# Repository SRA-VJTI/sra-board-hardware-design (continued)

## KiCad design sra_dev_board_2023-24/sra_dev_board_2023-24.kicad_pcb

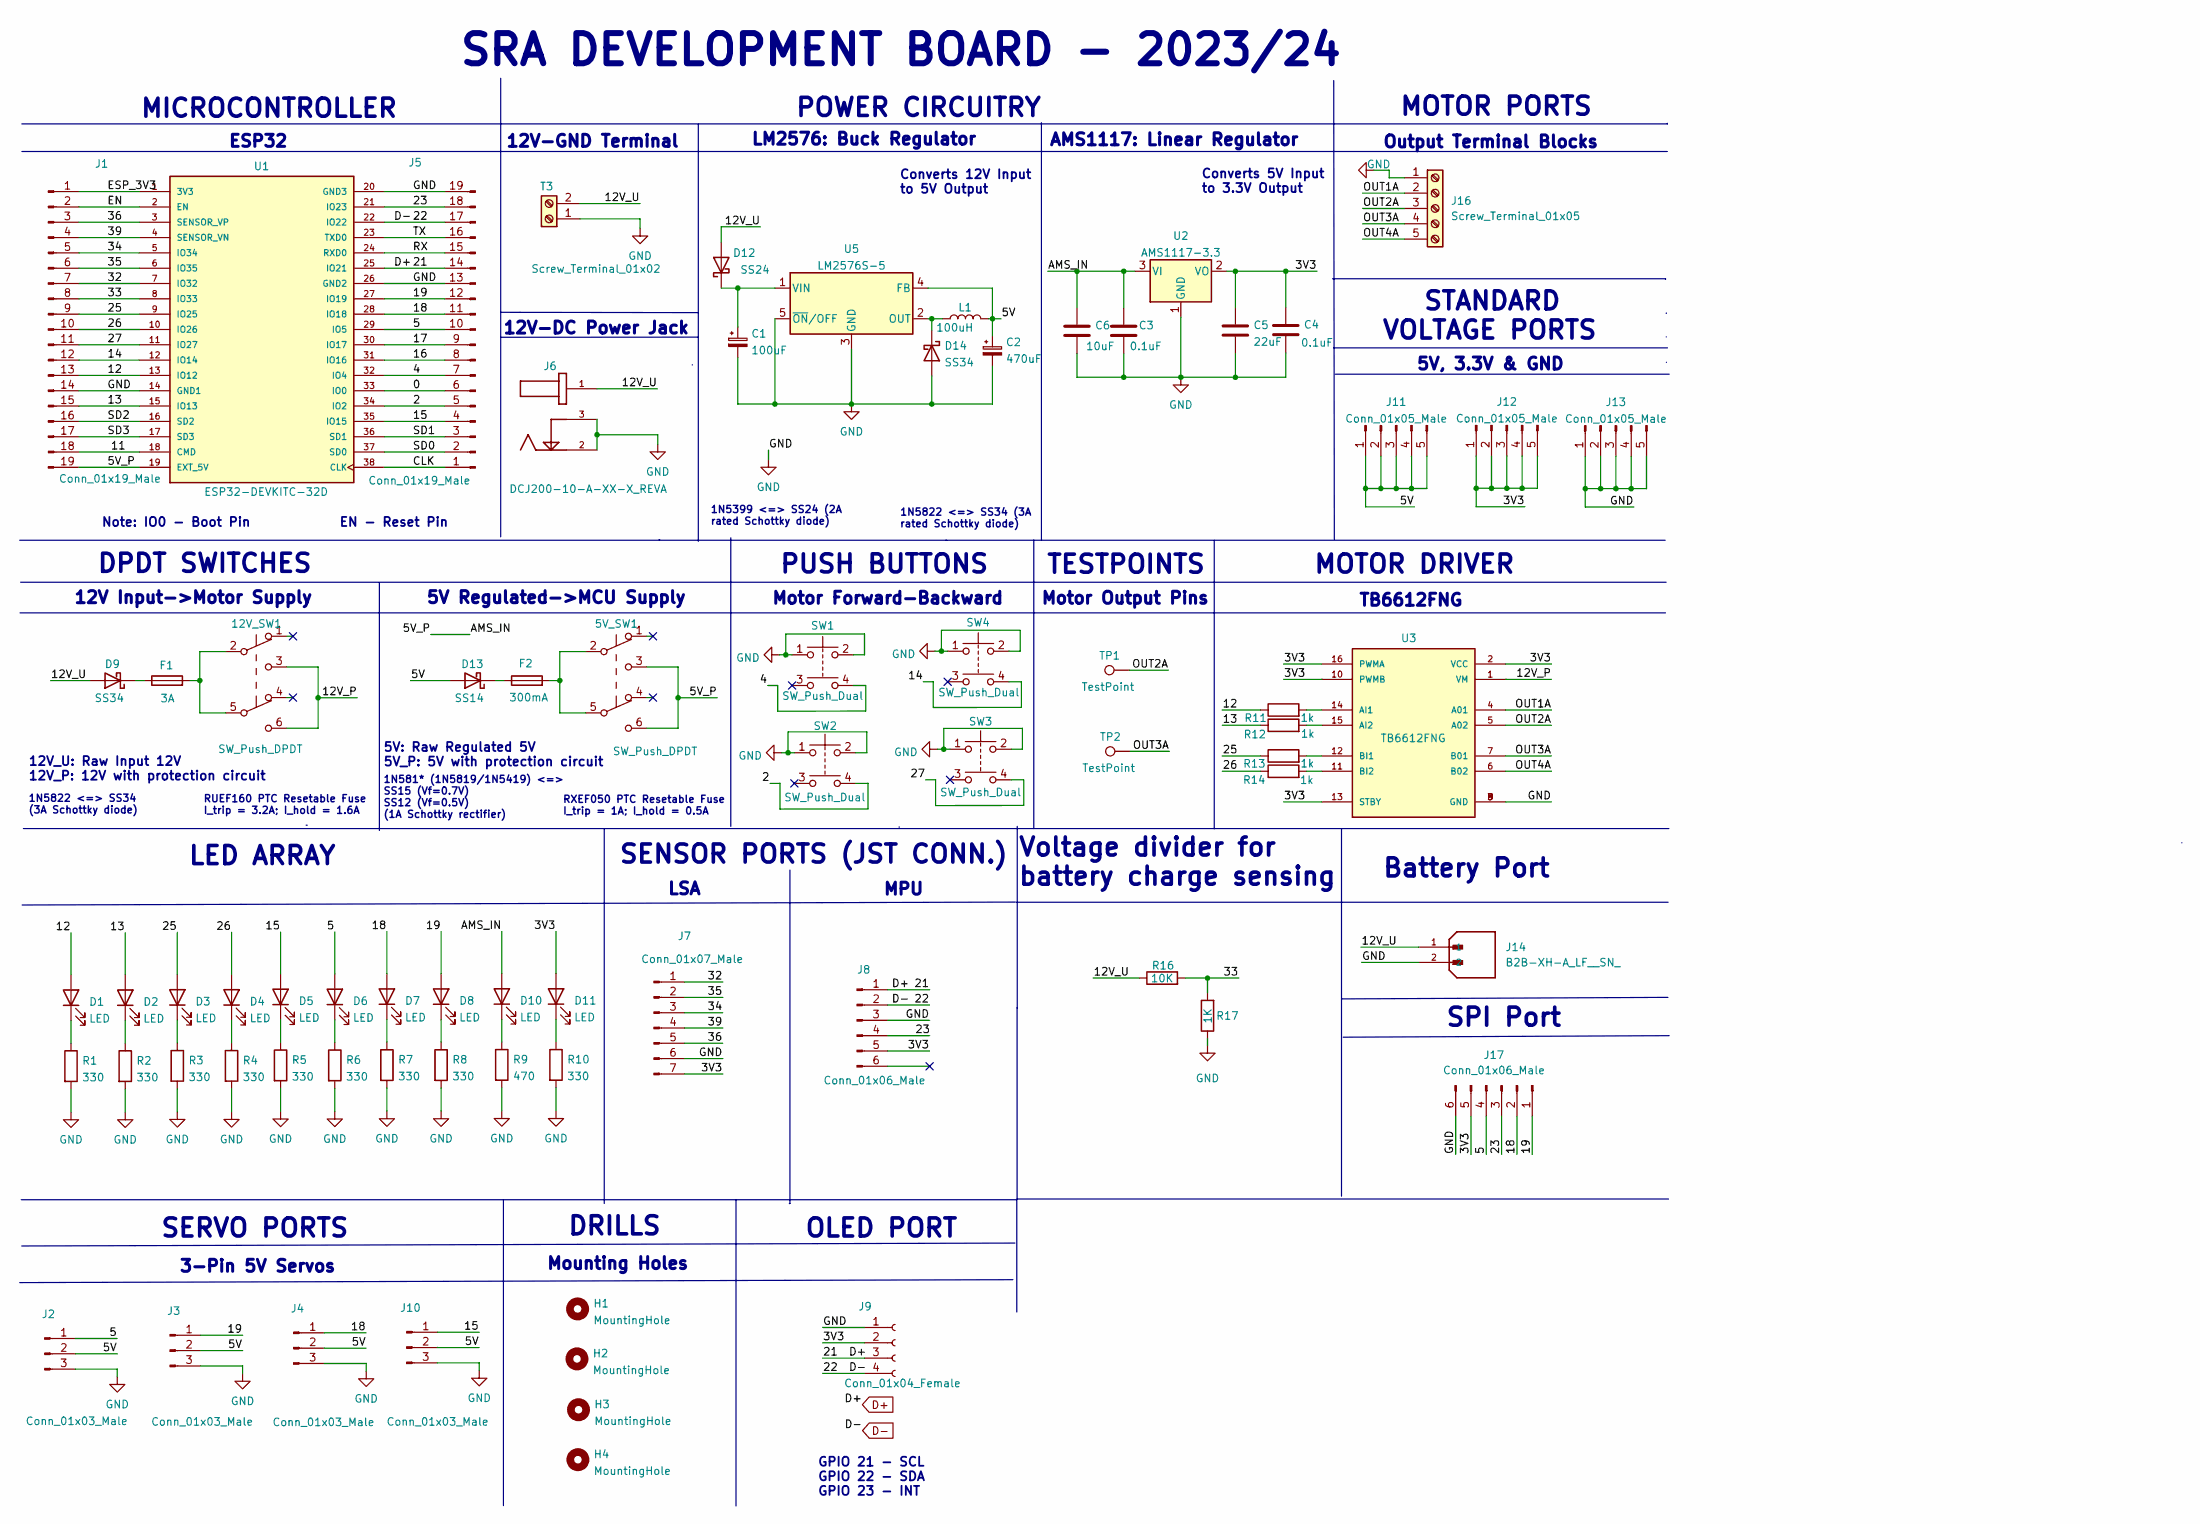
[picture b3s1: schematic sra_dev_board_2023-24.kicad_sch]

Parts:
5V_SW1, 12V_SW1: SW_Push_DPDT; dpdt_sw_2x03_tht
C1: 100uF; CP_Elec_6.3x7.7
C2: 470uF; CP_Elec_8x10
C3, C4: 0.1uF; C_0603_1608Metric
C5: 22uF; C_0603_1608Metric
C6: 10uF; C_0603_1608Metric
D1, D2, D3, D4, D5, D6, D7, D8, D10, D11: LED; LED_0603_1608Metric
D9, D14: SS34; D_SMB
D12: SS24; D_SMA
D13: SS14; D_SMA
F1: 3A; RUEF160
F2: 300mA; RXEF050
H1, H2, H3, H4: MountingHole; MountingHole_3.2mm_M3
J1, J5: Conn_01x19_Male; 1X19
J2, J3, J4, J10: Conn_01x03_Male; 1X03
J6: DCJ200-10-A-XX-X_REVA; BarrelJack_Wuerth_6941xx301002
J7: Conn_01x07_Male; PinHeader_1x07_P2.54mm_Vertical
J8, J17: Conn_01x06_Male; PinHeader_1x06_P2.54mm_Vertical
J9: Conn_01x04_Female; 1X04
J11, J12, J13: Conn_01x05_Male; 1X05
J14: B2B-XH-A_LF__SN_; JST_B2B-XH-A_LF__SN_; PARTREV N/A
J16: Screw_Terminal_01x05; TerminalBlock_bornier-5_P5.08mm
L1: 100uH; CDRH127_inductor_smd
R1, R2, R3, R4, R5, R6, R7, R8, R10: 330; R_0603_1608Metric
R9: 470; R_0603_1608Metric
R11, R12, R13, R14: 1k; R_1206_3216Metric
R16: 10K; R_1206_3216Metric
R17: 1K; R_1206_3216Metric
SW1, SW2, SW3, SW4: SW_Push_Dual; spst_tactile_sw_2x02_smd
T3: Screw_Terminal_01x02; 12V_1x02_tht
TP1, TP2: TestPoint; pad_1,27-2,54_smd
U1: ESP32-DEVKITC-32D; ESP32-DEVKITCv4-32D; PARTREV 4
U2: AMS1117-3.3; SOT-223-3_TabPin2
U3: TB6612FNG; TB6612FNG_2; PARTREV 11-13-17
U5: LM2576S-5; TO-263-5_TabPin3

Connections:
/0: J5.6, U1.33 (IO0)
/2: J5.5, SW2.4, U1.34 (IO2)
/3V3: C4.1, C5.1, D11.2 (A), J7.7, J8.5, J9.2, J12.1, J12.2, J12.3, J12.4, J12.5, J17.5, U2.2 (VO), U3.2 (VCC), U3.10 (PWMB), U3.13 (STBY), U3.16 (PWMA)
/4: J5.7, SW1.4, U1.32 (IO4)
/5: D6.2 (A), J2.1, J5.10, J17.4, U1.29 (IO5)
/5V: C2.1, D13.2 (A), J2.2, J3.2, J4.2, J10.2, J11.1, J11.2, J11.3, J11.4, J11.5, L1.2, U5.4 (FB)
/5V_P: 5V_SW1.3 (C), 5V_SW1.6 (C), C3.1, C6.1, D10.2 (A), J1.19, U1.19 (EXT_5V), U2.3 (VI)
/11: J1.18, U1.18 (CMD)
/12: D1.2 (A), J1.13, R11.1, U1.13 (IO12)
/12V_P: 12V_SW1.3 (C), 12V_SW1.6 (C), U3.1 (VM)
/12V_U: D9.2 (A), D12.2 (A), J6.1, J14.1, R16.1, T3.2
/13: D2.2 (A), J1.15, R12.1, U1.15 (IO13)
/14: J1.12, SW4.4, U1.12 (IO14)
/15: D5.2 (A), J5.4, J10.1, U1.35 (IO15)
/16: J5.8, U1.31 (IO16)
/17: J5.9, U1.30 (IO17)
/18: D7.2 (A), J4.1, J5.11, J17.2, U1.28 (IO18)
/19: D8.2 (A), J3.1, J5.12, J17.1, U1.27 (IO19)
/23: J5.18, J8.4, J17.3, U1.21 (IO23)
/25: D3.2 (A), J1.9, R13.1, U1.9 (IO25)
/26: D4.2 (A), J1.10, R14.1, U1.10 (IO26)
/27: J1.11, SW3.4, U1.11 (IO27)
/32: J1.7, J7.1, U1.7 (IO32)
/33: J1.8, R16.2, R17.2, U1.8 (IO33)
/34: J1.5, J7.3, U1.5 (IO34)
/35: J1.6, J7.2, U1.6 (IO35)
/36: J1.3, J7.5, U1.3 (SENSOR_VP)
/39: J1.4, J7.4, U1.4 (SENSOR_VN)
/CLK: J5.1, U1.38 (CLK)
/EN: J1.2, U1.2 (EN)
/ESP_3V3: J1.1, U1.1 (3V3)
/OUT1A: J16.2, U3.4 (A01)
/OUT2A: J16.3, TP1.1, U3.5 (A02)
/OUT3A: J16.4, TP2.1, U3.7 (B01)
/OUT4A: J16.5, U3.6 (B02)
/RX: J5.15, U1.24 (RXD0)
/SD0: J5.2, U1.37 (SD0)
/SD1: J5.3, U1.36 (SD1)
/SD2: J1.16, U1.16 (SD2)
/SD3: J1.17, U1.17 (SD3)
/TX: J5.16, U1.23 (TXD0)
D+: J5.14, J8.1, J9.3, U1.25 (IO21)
D-: J5.17, J8.2, J9.4, U1.22 (IO22)
GND: C1.2, C2.2, C3.2, C4.2, C5.2, C6.2, D14.2 (A), J1.14, J2.3, J3.3, J4.3, J5.13, J5.19, J6.2, J6.3, J7.6, J8.3, J9.1, J10.3, J13.1, J13.2, J13.3, J13.4, J13.5, J14.2, J16.1, J17.6, R1.2, R2.2, R3.2, R4.2, R5.2, R6.2, R7.2, R8.2, R9.2, R10.2, R17.1, SW1.1, SW1.2, SW2.1, SW2.2, SW3.1, SW3.2, SW4.1, SW4.2, T3.1, U1.14 (GND1), U1.20 (GND3), U1.26 (GND2), U2.1 (GND), U3.3 (GND), U3.8 (GND), U3.9 (GND), U5.3 (GND), U5.5 (~ON/OFF)
unnamed: 5V_SW1.2 (B), 5V_SW1.5 (B), F2.2
unnamed: 12V_SW1.2 (B), 12V_SW1.5 (B), F1.2
unnamed: D1.1 (K), R1.1
unnamed: D2.1 (K), R2.1
unnamed: D3.1 (K), R3.1
unnamed: D4.1 (K), R4.1
unnamed: D5.1 (K), R5.1
unnamed: D6.1 (K), R6.1
unnamed: D7.1 (K), R7.1
unnamed: D8.1 (K), R8.1
unnamed: D9.1 (K), F1.1
unnamed: D10.1 (K), R9.1
unnamed: D11.1 (K), R10.1
unnamed: C1.1, D12.1 (K), U5.1 (VIN)
unnamed: D13.1 (K), F2.1
unnamed: D14.1 (K), L1.1, U5.2 (OUT)
unnamed: R11.2, U3.14 (AI1)
unnamed: R12.2, U3.15 (AI2)
unnamed: R13.2, U3.12 (BI1)
unnamed: R14.2, U3.11 (BI2)

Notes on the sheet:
5V, 3.3V & GND
RXEF050 PTC Resetable Fuse I_trip = 1A; I_hold = 0.5A
Mounting Holes
SRA DEVELOPMENT BOARD - 2023/24
LED ARRAY
12V_U: Raw Input 12V 12V_P: 12V with protection circuit
12V-GND Terminal
1N5822 <=> SS34 (3A rated Schottky diode)
Output Terminal Blocks
LSA
MPU
Converts 5V Input to 3.3V Output
DRILLS
SENSOR PORTS (JST CONN.)
1N5399 <=> SS24 (2A rated Schottky diode)
DPDT SWITCHES
5V: Raw Regulated 5V 5V_P: 5V with protection circuit
Note: IO0 - Boot Pin EN - Reset Pin
POWER CIRCUITRY
ESP32
RUEF160 PTC Resetable Fuse I_trip = 3.2A; I_hold = 1.6A
LM2576: Buck Regulator
MICROCONTROLLER
Battery Port
GPIO 21 - SCL GPIO 22 - SDA GPIO 23 - INT
TB6612FNG
1N5822 <=> SS34 (3A Schottky diode)
3-Pin 5V Servos
SERVO PORTS
Voltage divider for battery charge sensing
1N581* (1N5819/1N5419) <=> SS15 (Vf=0.7V) SS12 (Vf=0.5V) (1A Schottky rectifier)
12V Input->Motor Supply
SPI Port
5V Regulated->MCU Supply
OLED PORT
MOTOR PORTS
Motor Output Pins
MOTOR DRIVER
12V-DC Power Jack
Converts 12V Input to 5V Output

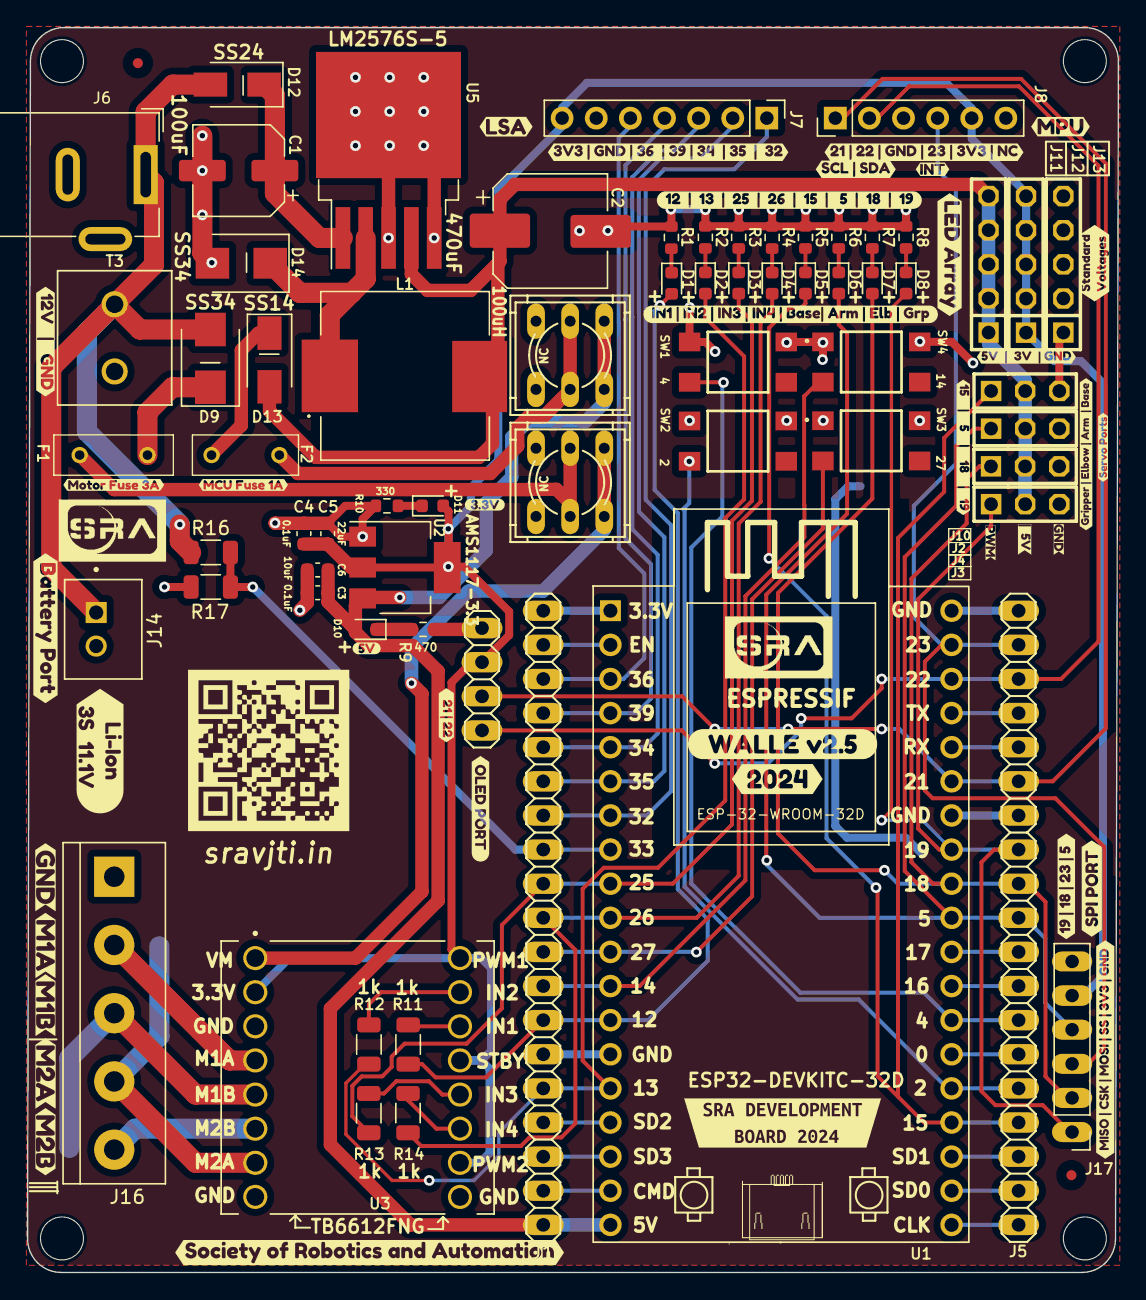
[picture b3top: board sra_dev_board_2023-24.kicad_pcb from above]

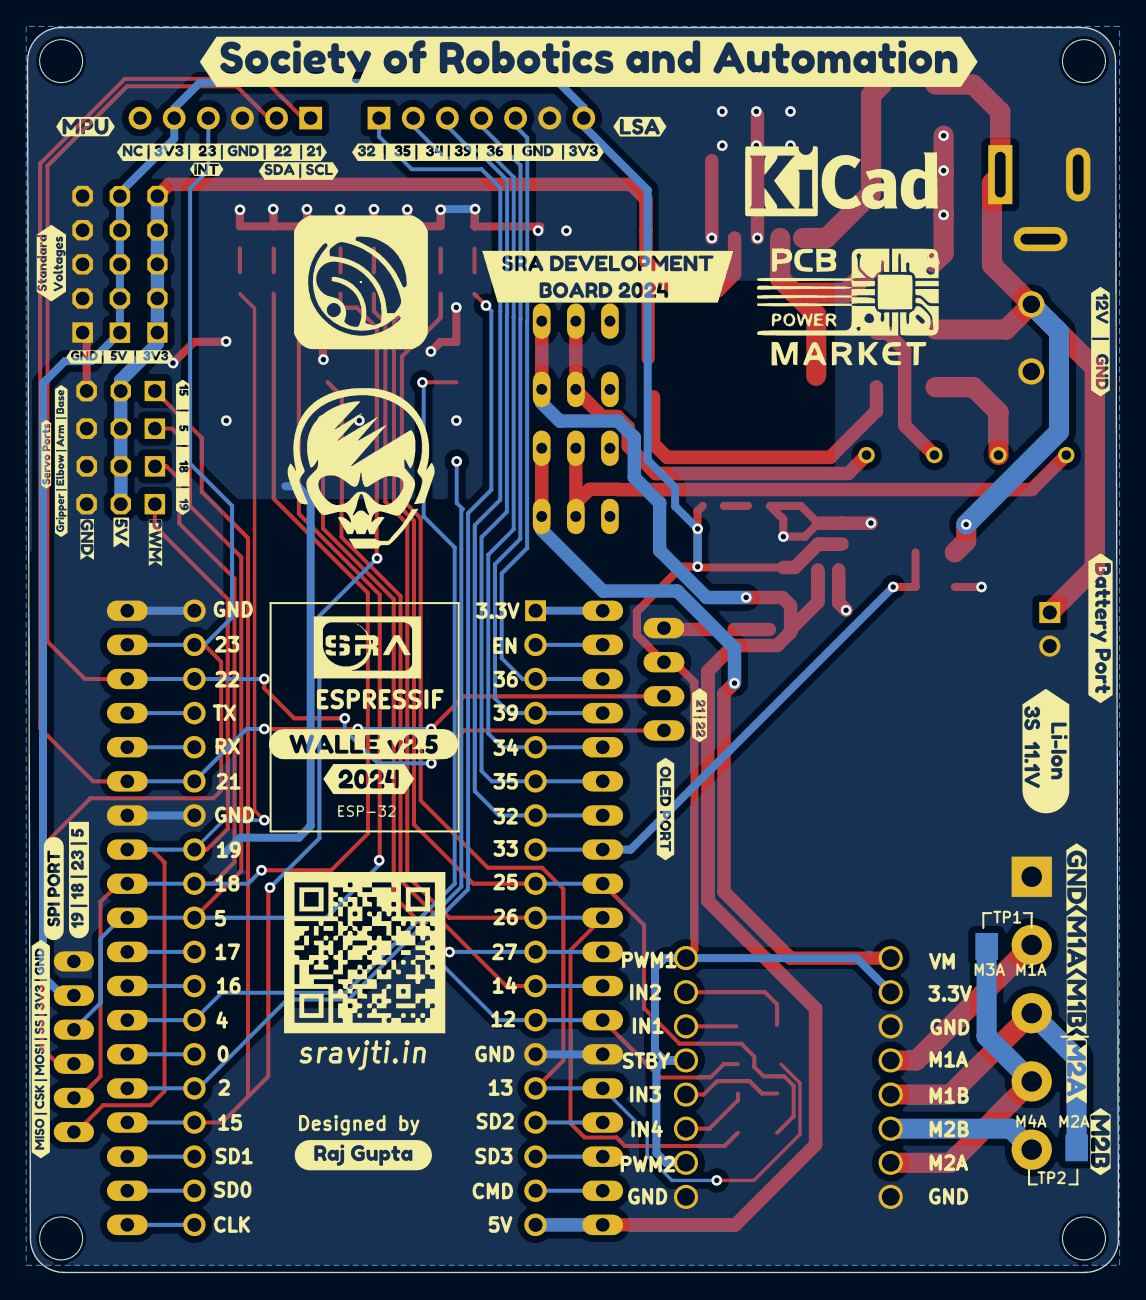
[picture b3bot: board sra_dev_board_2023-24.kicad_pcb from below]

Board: 2 copper layers, 81.2 x 92.7 mm, 142 parts (32 on the bottom side), 64 nets.

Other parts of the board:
kibuzzard-637A08DA, kibuzzard-637A08DA#2: G***; kibuzzard-637A08DA
kibuzzard-637B5F12: G***; kibuzzard-637B5F12
kibuzzard-637B5F60: G***; kibuzzard-637B5F60
kibuzzard-637B65B8: G***; kibuzzard-637B65B8
kibuzzard-658F2ACB: G***; kibuzzard-658F2ACB
kibuzzard-658F2B02: G***; kibuzzard-658F2B02
kibuzzard-658F2B2A: G***; kibuzzard-658F2B2A
kibuzzard-658F2C3C, kibuzzard-658F2C3C#2: G***; kibuzzard-658F2C3C
kibuzzard-658F2C13, kibuzzard-658F2C13#2: G***; kibuzzard-658F2C13
kibuzzard-658F2C67, kibuzzard-658F2C67#2: G***; kibuzzard-658F2C67
kibuzzard-658F2DCD: G***; kibuzzard-658F2DCD
kibuzzard-658F2DEA: G***; kibuzzard-658F2DEA
kibuzzard-658F2DF6: G***; kibuzzard-658F2DF6
kibuzzard-658F2E2C, kibuzzard-658F2E2C#2: G***; kibuzzard-658F2E2C
kibuzzard-658F2E4A, kibuzzard-658F2E4A#2: G***; kibuzzard-658F2E4A
kibuzzard-658F2E5A, kibuzzard-658F2E5A#2: G***; kibuzzard-658F2E5A
kibuzzard-658F2E6C, kibuzzard-658F2E6C#2: G***; kibuzzard-658F2E6C
kibuzzard-658F9F93, kibuzzard-658F9F93#2: G***; kibuzzard-658F9F93
kibuzzard-658F9FD8: G***; kibuzzard-658F9FD8
kibuzzard-658F289E: G***; kibuzzard-658F289E
kibuzzard-658F2903: G***; kibuzzard-658F2903
kibuzzard-658FA1D8: G***; kibuzzard-658FA1D8
kibuzzard-658FA19E: G***; kibuzzard-658FA19E
kibuzzard-658FA187, kibuzzard-658FA187#2: G***; kibuzzard-658FA187
kibuzzard-658FA201: G***; kibuzzard-658FA201
kibuzzard-6587FF3E: G***; kibuzzard-6587FF3E
kibuzzard-6587FF20: G***; kibuzzard-6587FF20
kibuzzard-6587FF29: G***; kibuzzard-6587FF29
kibuzzard-63775DBB, kibuzzard-63775DBB#2: G***; kibuzzard-63775DBB
kibuzzard-63777F1B: G***; kibuzzard-63777F1B
kibuzzard-65916C1A: G***; kibuzzard-65916C1A
kibuzzard-65916C11: G***; kibuzzard-65916C11
kibuzzard-65916C31: G***; kibuzzard-65916C31
kibuzzard-65916C76, kibuzzard-65916C76#2: G***; kibuzzard-65916C76
kibuzzard-65916D2D, kibuzzard-65916D2D#2: G***; kibuzzard-65916D2D
kibuzzard-653918A0: G***; kibuzzard-653918A0
kibuzzard-653918AE: G***; kibuzzard-653918AE
kibuzzard-653918C1: G***; kibuzzard-653918C1
kibuzzard-659161DE: G***; kibuzzard-659161DE
kibuzzard-659162C0: G***; kibuzzard-659162C0
kibuzzard-659163CD: G***; kibuzzard-659163CD
kibuzzard-659163E0: G***; kibuzzard-659163E0
kibuzzard-659164BA: G***; kibuzzard-659164BA
kibuzzard-659189BF, kibuzzard-659189BF#2: G***; kibuzzard-659189BF
kibuzzard-659189DA, kibuzzard-659189DA#2: G***; kibuzzard-659189DA
kibuzzard-6539189A: G***; kibuzzard-6539189A
kibuzzard-6591639C: G***; kibuzzard-6591639C
kibuzzard-6591649B: G***; kibuzzard-6591649B
kibuzzard-6591664B: G***; kibuzzard-6591664B
kibuzzard-6591665D: G***; kibuzzard-6591665D
kibuzzard-65916111: G***; kibuzzard-65916111
kibuzzard-65916213: G***; kibuzzard-65916213
kibuzzard-65918321: G***; kibuzzard-65918321
kibuzzard-65919040, kibuzzard-65919040#2: G***; kibuzzard-65919040

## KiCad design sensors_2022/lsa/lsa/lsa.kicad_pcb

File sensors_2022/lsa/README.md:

## LSA - Light Sensor Array

### Table of Contents
* [Overview](#overview)
* [Features](#features)
* [Components of LSA](#components-of-lsa)
* [Function of Components](#function-of-components)
	* [LED](#function-of-components)
	* [PhotoDiode](#function-of-components)
	* [IC LM324](#function-of-components)
	* [Resistors](#function-of-components)
* [Connections](#connections)
* [Working Principle](#working-principle)
* [Appplications](#applications)
* [Scope of Improvement](#scope-of-improvement)

### Overview 
- The Light Sensor Array(LSA) is used to detect the white/black lined surface and it sends this data to the microcontroller ESP-32. Analyzing and processing the data received by the microcontroller ESP-32, the purpose of line following is achieved.

- Physical PCB

- PCB Backside

### Features
* Components used are readily available.
* Easy connections for output signals.
* Compact enough to fit into any project.
* Distinguished trace widths for Signal and Power Routes.

### Components of LSA
| Component   | Description   | Quantity |
| ----------- | ------------- | -------- |
| LED         | Emits light   |  4       |
| PhotoDiode  | Absorbs light |  4       |
| IC LM324    | Op.Amp. IC    |  1       |  
| Resistors   | Limit Current |  8       |
|JST Connector | Connect PCB with other circuits|1|

### Function of Components
- LED
	- LSA consists of Four LED and PhotoDiode Pairs. The specific LED's emit white light which is incident on the surface and some of it is absorbed by the surface. The voltage source For the LEDs to glow is VCC.

- PhotoDiode
	- Based upon the reflectivity coefficient of the surface( generally less than 1), the remaining light reflected from the surface is captured by the Photodiodes. LEDs and complimentary photodiodes are used to efficiently detect the surface (white/black line) as the environment also contains unwanted light for the LSA sensor. The amount of light received is directly proportional to the current generated by it. More the light, more the current, more the reading.
 
- IC LM324 
	- This is a Quad(4) OP.Amp. IC. Op.Amp i.e Operation Amplifiers amplify the current with constant volatge. Since the current reading from photo diodes is significantly small and difficult to compare, it needs to be amplified. The 4 amplified outputs serve as raw readings of LSA.

- Resistors
	- Now to limit the current and thus to protect the LEDs, PhotoDiodes current limiting resistors are used.

### Connections
To connect LSA with the SRA Board, connect the JST connector in the following way:

### Working Principle
- LSA works on the principle of reflectivity of light for different types of surfaces.
	- Black Surface -> HIGH absorptivity -> LESS reflectivity
	- White Surface -> LOW absorptivity -> HIGH reflectivity
- Demonstration

### Applications
* Obstacle detection on a clear path.
* Line Following.
* Distinguish Colours on a path.

### Scope of Improvement
- LSA sometimes provides slightly inaccurate readings due to external light and conditions due to non uniformity of the colour of the path. Therefore, LSA has low accuracy. Hence LSA should be kept close to the ground.
- As of now only white and black surfaces are being mapped. Given accurate sensors and proper mapping we can map LSA for any range of RGB colours.

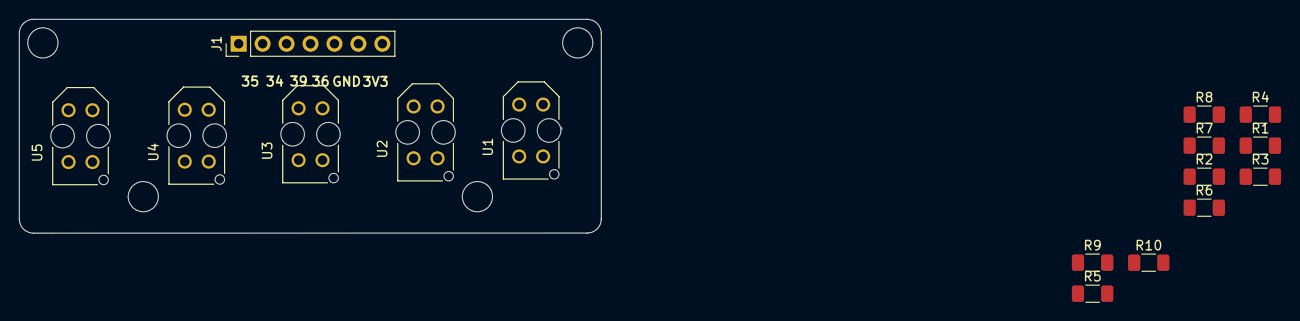
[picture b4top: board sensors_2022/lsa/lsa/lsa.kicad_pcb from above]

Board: 2 copper layers, 61.7 x 22.7 mm, 16 parts (0 on the bottom side), 12 nets.

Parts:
J1: Conn_01x07_Male; PinHeader_1x07_P2.54mm_Vertical
R1, R3, R5, R7, R9: 150E; R_1206_3216Metric_Pad1.30x1.75mm_HandSolder
R2, R4, R6, R8, R10: 4.7k; R_1206_3216Metric_Pad1.30x1.75mm_HandSolder
U1, U2, U3, U4, U5: TCRT5000; OPTO_TCRT5000

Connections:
+3V3: J1.7, R1.1, R2.2, R3.1, R4.2, R5.1, R6.2, R7.1, R8.2, R9.1, R10.2
/A0_36: J1.5, R2.1, U1.E
/A1_39: J1.4, R4.1, U2.E
/A2_34: J1.3, R6.1, U3.E
/A3_35: J1.2, R8.1, U4.E
/A4_32: J1.1, R10.1, U5.E
GND: J1.6, U1.A, U1.COLL, U2.A, U2.COLL, U3.A, U3.COLL, U4.A, U4.COLL, U5.A, U5.COLL
unnamed: R1.2, U1.CATH
unnamed: R3.2, U2.CATH
unnamed: R5.2, U3.CATH
unnamed: R7.2, U4.CATH
unnamed: R9.2, U5.CATH

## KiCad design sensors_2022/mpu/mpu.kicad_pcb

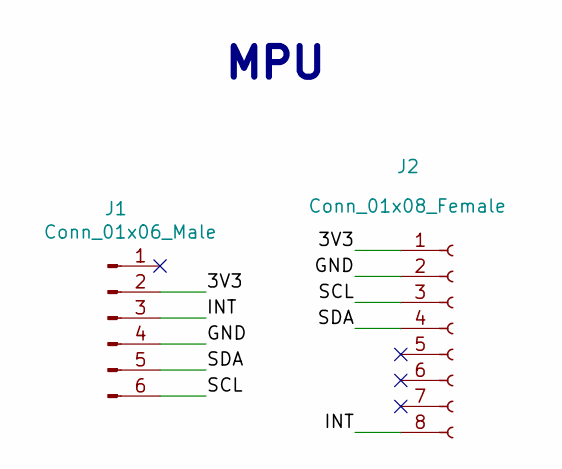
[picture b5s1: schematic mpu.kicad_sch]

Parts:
J1: Conn_01x06_Male; PinHeader_1x06_P2.54mm_Vertical
J2: Conn_01x08_Female; 1X08

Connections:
Board_0-/3V3: J1.2, J2.1
Board_0-/GND: J1.4, J2.2
Board_0-/INT: J1.3, J2.8
Board_0-/SCL: J1.6, J2.3
Board_0-/SDA: J1.5, J2.4
Board_0-unconnected-(J1-Pad1): J1.1
Board_0-unconnected-(J2-Pad5): J2.5
Board_0-unconnected-(J2-Pad6): J2.6
Board_0-unconnected-(J2-Pad7): J2.7

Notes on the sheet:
MPU

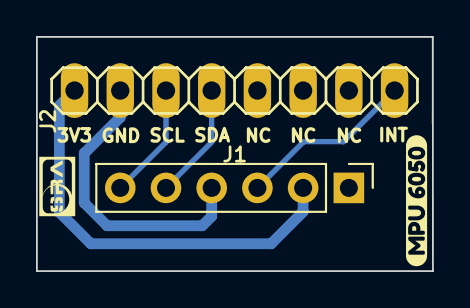
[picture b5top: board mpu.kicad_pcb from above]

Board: 2 copper layers, 22.0 x 13.0 mm, 3 parts (0 on the bottom side), 5 nets.

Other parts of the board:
kibuzzard-61F904D7: G***; kibuzzard-61F904D7

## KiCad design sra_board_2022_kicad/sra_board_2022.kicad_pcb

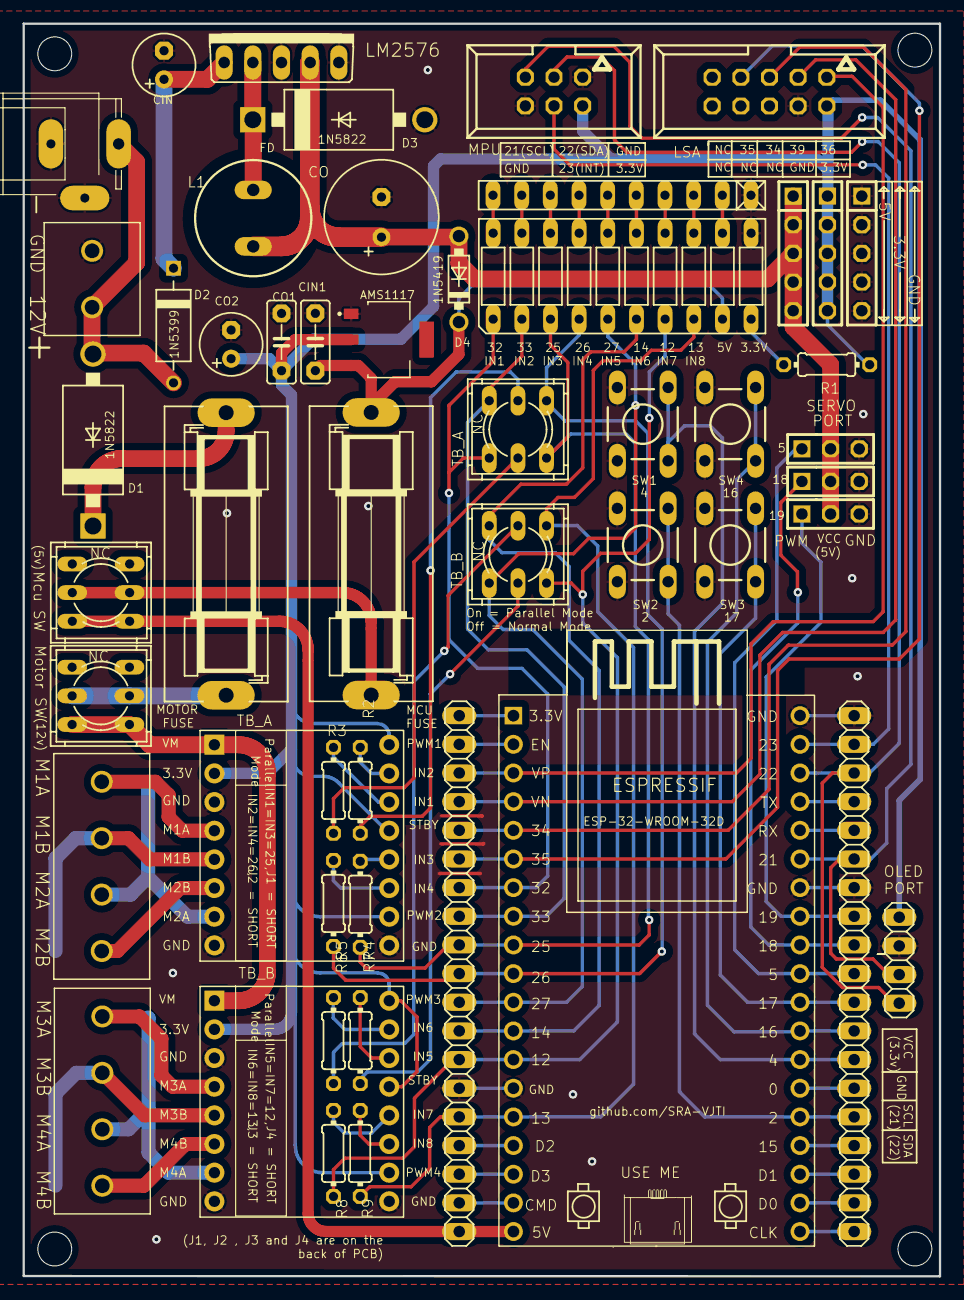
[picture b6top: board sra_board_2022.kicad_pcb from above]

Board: 2 copper layers, 81.2 x 111.0 mm, 59 parts (0 on the bottom side), 76 nets.

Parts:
12V: 691131710002
@HOLE0, @HOLE1, @HOLE2, @HOLE3: (no value)
AMS1117: AMS1117-3.3; SOT229P700X180-4N
CIN: 100uF; E2,5-6
CIN1: 0.1uF; C5B2.5
CO: 470uF; E3,5-10
CO1: 0.1uF; C5B2.5
CO2: 22uF; E2,5-6
D1: 1N5817-B; DO41-7.6
F2, F3: 3A; SH25
J1, J2: 691131710004
JP1, JP2: 1X19
JP3, JP5, JP8: 1X03
JP4, JP6, JP7, JP10: 1X05
L1: 100uH; SD12K100
LDZ1: LB10
LINE-SENSOR: 057-010-1
MCU-S/W: 9077-2
MOTOR-S/W: 9077-2
OLED: 1X04
PAD1, PAD2, PAD3, PAD4: SMD1,27-2,54
POWER-JACK: SPC4078
R1: 470Ω; 0204_7
R2, R3, R4, R5, R6, R7, R8, R9: 1KΩ; 0204_7
RN2: RN-10
SW1, SW2, SW3, SW4: DTS-6
TB1, TB2: TB6612FNG
TB_A: 9077-2
TB_B: 9077-2
U1: ESP32-DEVKITC-32D; MODULE_ESP32-DEVKITC-32D
U$1, U$2: 1N5399_SQUARE; C2673
U$3: 1N5399_ROUND; D-10
X1: 057-006-1

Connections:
0: 12V.1, AMS1117.1, CIN.-, CIN1.1, CO.-, CO1.1, CO2.-, JP1.1, JP1.7, JP2.6, JP3.3, JP4.1, JP4.2, JP4.3, JP4.4, JP4.5, JP5.3, JP6.3, JP6.5, JP8.3, LDZ1.11, LINE-SENSOR.4, OLED.2, POWER-JACK.1, POWER-JACK.2, RN2.1, SW1.3, SW1.4, SW2.3, SW2.4, SW3.3, SW3.4, SW4.3, SW4.4, TB1.GND1, TB1.GND2, TB1.GND3, TB2.GND1, TB2.GND2, TB2.GND3, U1.14, U1.20, U1.26, U$2.A, X1.1, X1.6
2: JP1.15, SW2.1, SW2.2, U1.34
2L: LDZ1.20, RN2.10
3.3V: AMS1117.2, CO1.2, CO2.+, JP10.1, JP10.2, JP10.3, JP10.4, JP10.5, LINE-SENSOR.2, OLED.1, R1.2, TB1.PWMA, TB1.PWMB, TB1.STBY, TB1.VCC, TB2.PWMA, TB2.PWMB, TB2.STBY, TB2.VCC, X1.2
3L: LDZ1.19, RN2.9
3V3: JP2.19, U1.1
4: JP1.13, SW1.1, SW1.2, U1.32
4L: LDZ1.18, RN2.8
5: JP1.10, JP8.1, U1.29
5L: LDZ1.17, RN2.7
5V: CO.+, D1.A, JP3.2, JP5.2, JP6.4, JP7.1, JP7.2, JP7.3, JP7.4, JP7.5, JP8.2, L1.1
5V_P: JP2.1, MCU-S/W.1, MCU-S/W.4, U1.19
5_AF: F2.1, MCU-S/W.2, MCU-S/W.5
6L: LDZ1.16, RN2.6
7L: LDZ1.15, RN2.5
8L: LDZ1.14, RN2.4
9L: LDZ1.13, RN2.3
10L: LDZ1.12, RN2.2
12: JP2.7, LDZ1.7, R8.2, TB_B.1, U1.13
12V_AF: F3.2, MOTOR-S/W.2, MOTOR-S/W.5
12V_P: MOTOR-S/W.1, MOTOR-S/W.4, TB1.VM, TB2.VM
12V_U: R3.1, TB1.AIN1
13: JP2.5, LDZ1.8, R9.2, TB_B.4, U1.15
14: JP2.8, LDZ1.6, TB_B.6, U1.12
15: JP1.16, U1.35
16: JP1.12, SW4.1, SW4.2, U1.31
17: JP1.11, SW3.1, SW3.2, U1.30
18: JP1.9, JP5.1, U1.28
19: JP1.8, JP3.1, U1.27
21: JP1.6, OLED.3, U1.25, X1.5
22: JP1.3, OLED.4, U1.22, X1.3
23: JP1.2, U1.21, X1.4
25: JP2.11, LDZ1.3, R4.2, TB_A.1, U1.9
26: JP2.10, LDZ1.4, R5.2, TB_A.4, U1.10
27: JP2.9, LDZ1.5, TB_B.3, U1.11
32: JP2.13, LDZ1.1, TB_A.3, U1.7
33: JP2.12, LDZ1.2, TB_A.6, U1.8
34: JP2.15, LINE-SENSOR.5, U1.5
35: JP2.14, LINE-SENSOR.7, U1.6
36: JP2.17, LINE-SENSOR.1, U1.3
39: JP2.16, LINE-SENSOR.3, U1.4
AIN1: R3.2, TB_A.2
AIN2: R2.2, TB_A.5
AMS_IN: AMS1117.3, CIN1.2, D1.C, F2.2, LDZ1.9
BIN1: R7.2, TB_B.2
BIN2: R6.2, TB_B.5
CLK: JP1.19, U1.38
CMD: JP2.2, U1.18
COB: R2.1, TB1.AIN2
COT: 12V.2, POWER-JACK.3, U$1.A, U$3.A
EN: JP2.18, U1.2
unnamed: LDZ1.10, R1.1
unnamed: R4.1, TB1.BIN1
unnamed: R5.1, TB1.BIN2
unnamed: R6.1, TB2.AIN2
unnamed: R7.1, TB2.AIN1
unnamed: R8.1, TB2.BIN1
unnamed: R9.1, TB2.BIN2
unnamed: F3.1, U$1.C
unnamed: CIN.+, JP6.1, U$3.C
unnamed: JP6.2, L1.2, U$2.C
O: JP1.14, U1.33
OUT1A: J1.1, TB1.A1
OUT1B: J2.1, TB2.A1
OUT2A: J1.2, PAD2.1, TB1.A2
OUT2B: J2.2, PAD4.1, TB2.A2
OUT3A: J1.3, PAD1.1, TB1.B1
OUT3B: J2.3, PAD3.1, TB2.B1
OUT4A: J1.4, TB1.B2
OUT4B: J2.4, TB2.B2
RX: JP1.5, U1.24
SD0: JP1.18, U1.37
SD1: JP1.17, U1.36
SD2: JP2.4, U1.16
SD3: JP2.3, U1.17
TX: JP1.4, U1.23

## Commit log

2020-09-04 README and Eagle files added
2020-09-04 External Eagle libraries added
2020-09-04 READE updated
2020-09-05 Gerber added and README updated
2020-09-05 README updated
2020-09-05 LOGO changed
2020-09-05 minor update
2020-09-05 Extra folder deleted
2020-09-05 Foldername changed
2020-09-05 foldername and filename changed
2020-09-05 foldername changed and README updated
2020-09-07 filename renamed
2020-09-07 Directory restructured, updated README
2020-09-09 minor fix in readme
2020-09-17 Datasheets Added
2020-09-17 ESP32 Hardware guideline Added
2021-01-10 Renamed Eagle files and Added Series Resistor Between ESP and Motor Driver
2021-01-10 OSH park tag added in README
2021-01-11 Change the placement of Series Resistors and cleaned the routing
2021-01-16 Mosfet Replaced by two individual Diodes
2021-01-23 Front and back silkscreen improved
2021-01-23 Added New Footprints
2021-01-23 Added Images of Final Board
2021-01-23 Gerber File added and readme updated
2022-01-08 Sensor eagle and kicad files added
2022-01-08 lsa files cleaned
2022-01-23 Imported SRA 2020 board eagle -> Kicad6, organised structure, footprint libs
2022-01-23 Updated year in README.md
2022-01-23 SRA Board 2022: Porting to Kicad 6.0 (#4)
    * Imported SRA 2020 board eagle -> Kicad6, organised structure, footprint libs
    * Updated year in README.md
2022-01-23 Corrected Schematics for KiCad 6
2022-01-30 Added project files for fresh 2022 SRA Dev Board
2022-01-31 Finalised SRA Dev Board 2022 Design, added gerbers, renders, assets
2022-01-31 Updated gerbers, board image assets
2022-01-31 Fixed names and images in sra_board_images.md
2022-01-31 Added Interactive BOM, SMT pick place files
2022-02-01 fixed untracked files
2022-02-01 Added PCB files for LSA and MPU 2022
2022-02-01 First prototype gerber files added, fixed project structure, kicad files
2022-02-06 Created a README for MPU 6050
2022-02-07 Merged the Wall-E and my README
2022-02-08 Updated SRA-board images, updated the 3d view image in assets fiolder under documentation folder & added LSA and MPU folder under documentationn/images
2022-02-08 updated the sra_board_images.md file
2022-02-08 LSA Readme added.
2022-02-08 LSA Readme updated.
2022-02-08 Minor changes made
2022-02-08 ESP Functions removed
2022-02-08 Connection edited
2022-02-08 Connection of MPU6050 with SRA Board
    Added image of MPU6050 connection with SRA Board
2022-02-08 images dimensions changed.
2022-02-08 readme name changed
2022-02-08 Renamed MPU readme file
2022-02-09 Added cad, step and .wrl files for lsa, mpu and sra_board under 3d_model folder
2022-02-09 Removed the other_components_model folder under 3d_models And renamed the sra_board_images.md to README.md
2022-02-10 SRA Board 2022 Doc
2022-02-10 3d-view of 2022 Board
2022-02-10 Image for FRC Connectors
2022-02-10 Image for JST-PH COnnectors
2022-02-10 2022 SRA board Doc
2022-02-10 Deleted jpeg file
2022-02-10 Image for JST PH Connectors
2022-02-13 Images aligned to center and Readme name changed.
2022-02-13 Image and gif dimensions changed.
2022-02-13 2022 Updated Doc
2022-02-14 Asset folder in lsa removed and moved the content to documentation.
2022-02-14 Sources of images and gif changed in README
2022-02-19 Documentation for SRA Board 2022
2022-02-22 Testing documentation website
2022-03-06 SRA Board, MPU, LSA Kicad, Gerber files updated
2022-08-28 Update README.md Add renders, datasheets, documentation
2022-11-01 Fixed readme errors
2022-11-03 add DRV8825 Stepper Driver
2022-11-10 Add footprint and symbol for DRV8825 and update schematic
2022-11-10 Modify routing according to new schematic
2022-11-10 modify silkscreen
2022-11-11 add TCRT-5000 base structure to LSA
2022-11-13 Update PCBs for Wall-E 2023
    Additions:
    1. Add new LSA
    2. Add new fabrication outputs for SRA board and LSA.
    3. Add terminal block for ground connection for shielding.
    Modifications:
    1. Modify MCU switch placement.
2022-11-20 Updated gerbers for LSA and SRA-Board
2022-11-22 Updated working content for sra_dev_board_2023
2022-11-22 updated BoM for sra_board_2023
2022-11-22 Add 3D model for TCRT5000
2022-11-22 Tweaks in routing prototype-1
2022-11-23 Add updated 3d renders for sra-dev-board-2023
2022-12-10 Resolve LSA wiring problem and fixed silkscreen, updated gerbers, fabrication outputs and 3D files for LSA
2022-12-15 Update LSA and SRA board after hardware testing
2023-01-09 Update repo with recent changes
2023-01-11 Modify relative path for TCRT5000 footprint
2023-01-13 added
2023-01-19 Motor Driver images changed
2023-01-26 added pinout diagrams for mpu,lsa and sra boards
2023-01-27 changed README to include pinout images and made changes to README with latest changes
2023-01-27 fixed README to show images
2023-02-02 removed unnecessary files
2023-02-21 Add current limiting resistor on Interrupt line for MPU
2023-02-21 Update gerbers, placement files and BoM
2023-03-26 Minor changes to README for new SRA BOARD, added new images
2023-03-26 minor changes
2023-03-30 Updates to README for SRA BOARD 2023 (#25)
    * added pinout diagrams for mpu,lsa and sra boards
    * changed README to include pinout images and made changes to README with latest changes
    * fixed README to show images
    * Minor changes to README for new SRA BOARD, added new images
    * minor changes
2023-03-30 Add current limiting resistor for MPU (#26)
    * Add current limiting resistor on Interrupt line for MPU
    * Update gerbers, placement files and BoM
2024-05-10 SRA Board 2023-24 Updated
2024-05-10 Readme SRA Board Updated
2024-05-10 Parallel Mode Removed
2024-05-14 SRA Board 23-24 Updated
2025-04-10 Fixes: addressed PR review comments
2025-06-25 Revert "Updated Readme and assets for SRA board 2024-25"
2025-06-25 Update the assets and readme as per SRA Board 2024-25 (#33)
2026-03-06 SRA Board 2025-26 Update
2026-03-07 readme update for 2025-26 SRA Board
2026-03-14 Update for the SRA Board 2025-26 (#34)
    * SRA Board 2025-26 Update
    * readme update for 2025-26 SRA Board
